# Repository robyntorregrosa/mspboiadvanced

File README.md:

# mspboiadvanced
a handheld game console in msp430 

table of contents:

gameboi.c - this is the important part of the project that runs the game on the LED board

rand.c - used for randomly placing berries on the board

snake.c - attempt at making a FIFO snake struct

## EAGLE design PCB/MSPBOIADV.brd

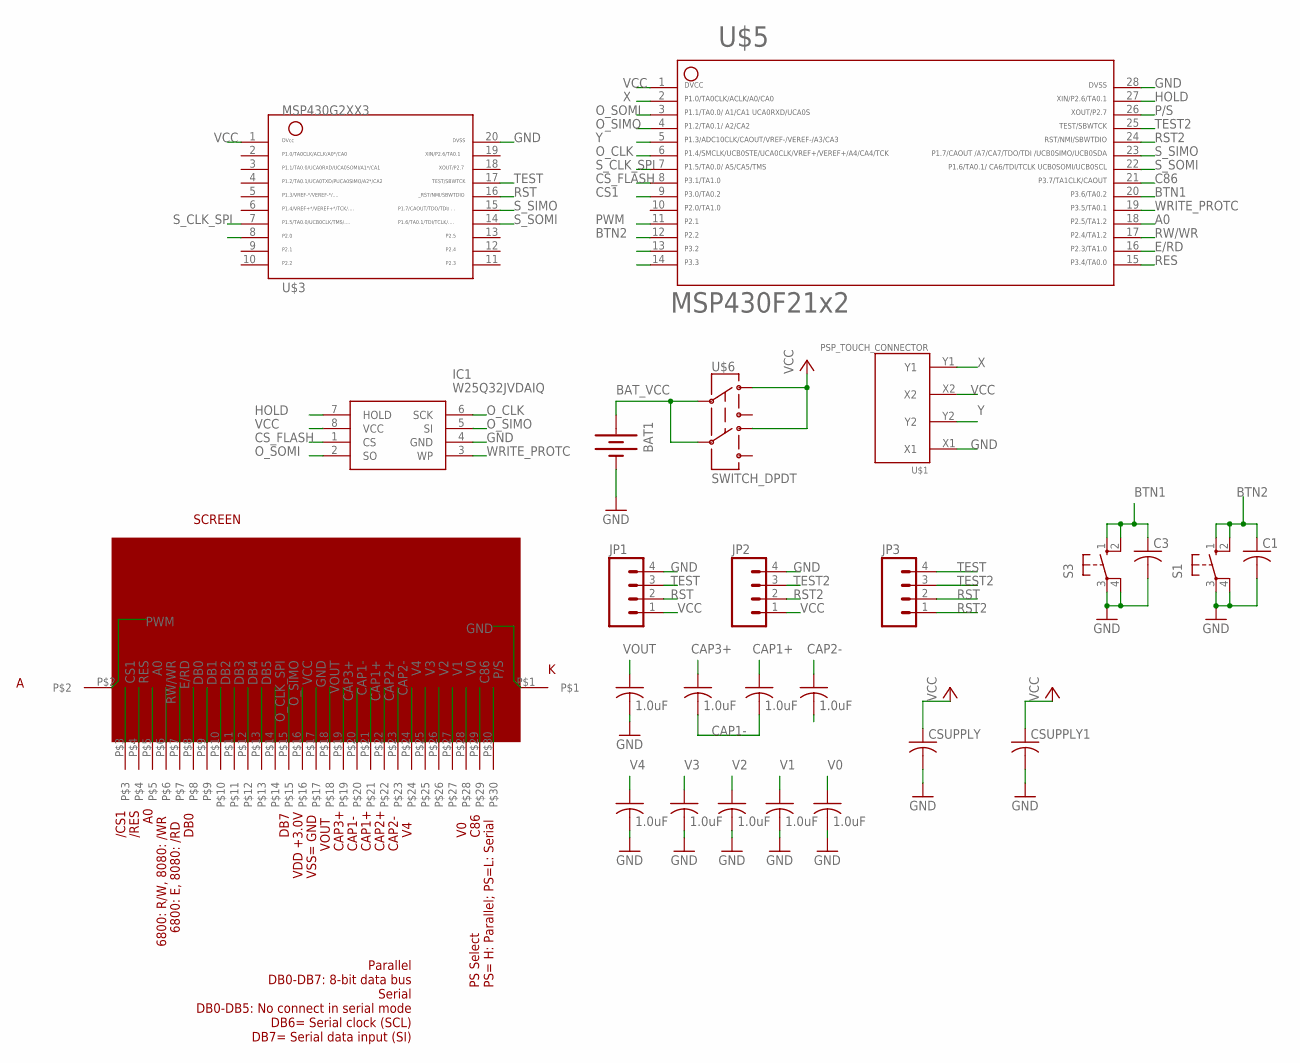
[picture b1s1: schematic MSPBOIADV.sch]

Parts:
1.0UF, 1.0UF1: 1.0uF; C1206
BAT1: BATTERY; BATTERY_PACK_2AA
C1, C3: C-USC1206; C1206
CSUPPLY, CSUPPLY1: C-USC1206; C1206
IC1: W25Q32JVDAIQ; DIP902W46P254L959H533Q8N
JP1, JP2, JP3: M04LOCK; 1X04_LOCK
S1, S3: 10-XX; B3F-10XX
U$1: PSP_TOUCH_CONNECTOR
U$2: SCREEN; DISPLAY_128_64
U$3: MSP430G2XX3TSSOP; PW20
U$5: USETHIS; PW28
U$6: SWITCH_DPDT; JS_DPDT_TH
VOUTCAP, VOUTCAP1, VOUTCAP2, VOUTCAP3, VOUTCAP4, VOUTCAP5, VOUTCAP6: 1.0uF; C1206

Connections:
A0: U$2.P$5, U$5.18
BAT_VCC: BAT1.3V (+), U$6.2, U$6.5
BTN1: C3.1, S3.1 (S), S3.2 (S1), U$5.20
BTN2: C1.1, S1.1 (S), S1.2 (S1), U$5.12
C86: U$2.P$29, U$5.21
CAP1+: 1.0UF1.1, U$2.P$21
CAP1-: 1.0UF.2, 1.0UF1.2, U$2.P$20
CAP2+: U$2.P$22, VOUTCAP1.2
CAP2-: U$2.P$23, VOUTCAP1.1
CAP3+: 1.0UF.1, U$2.P$19
CHP_SLCT: U$3.8
CS1: U$2.P$3, U$5.9
CS_FLASH: IC1.1 (CS), U$5.8
DB0: U$2.P$8
DB1: U$2.P$9
DB2: U$2.P$10
DB3: U$2.P$11
DB4: U$2.P$12
DB5: U$2.P$13
E/RD: U$2.P$7, U$5.16
GND: BAT1.GND (-), C1.2, C3.2, CSUPPLY.2, CSUPPLY1.2, IC1.4 (GND), JP1.4, JP2.4, S1.3, S1.4 (P1), S3.3, S3.4 (P1), U$1.X1, U$2.P$1, U$2.P$17, U$3.20, U$5.28, VOUTCAP.2, VOUTCAP2.2, VOUTCAP3.2, VOUTCAP4.2, VOUTCAP5.2, VOUTCAP6.2
HOLD: IC1.7 (HOLD), U$5.27
O_CLK: IC1.6 (SCK), U$5.6
O_CLK_SPI: U$2.P$14
O_SIMO: IC1.5 (SI), U$2.P$15, U$5.4
O_SOMI: IC1.2 (SO), U$5.3
P/S: U$2.P$30, U$5.26
PWM: U$2.P$2, U$5.11
RES: U$2.P$4, U$5.15
RST: JP1.2, JP3.2, U$3.16
RST2: JP2.2, JP3.1, U$5.24
RW/WR: U$2.P$6, U$5.17
S_CLK_SPI: U$3.7, U$5.7
S_SIMO: U$3.15, U$5.23
S_SOMI: U$3.14, U$5.22
TEST: JP1.3, JP3.4, U$3.17
TEST2: JP2.3, JP3.3, U$5.25
V0: U$2.P$28, VOUTCAP6.1
V1: U$2.P$27, VOUTCAP5.1
V2: U$2.P$26, VOUTCAP4.1
V3: U$2.P$25, VOUTCAP3.1
V4: U$2.P$24, VOUTCAP2.1
VCC: CSUPPLY.1, CSUPPLY1.1, IC1.8 (VCC), JP1.1, JP2.1, U$1.X2, U$2.P$16, U$3.1, U$5.1, U$6.1, U$6.4
VOUT: U$2.P$18, VOUTCAP.1
WRITE_PROTC: IC1.3 (WP), U$5.19
X: U$1.Y1, U$5.2
Y: U$1.Y2, U$5.5

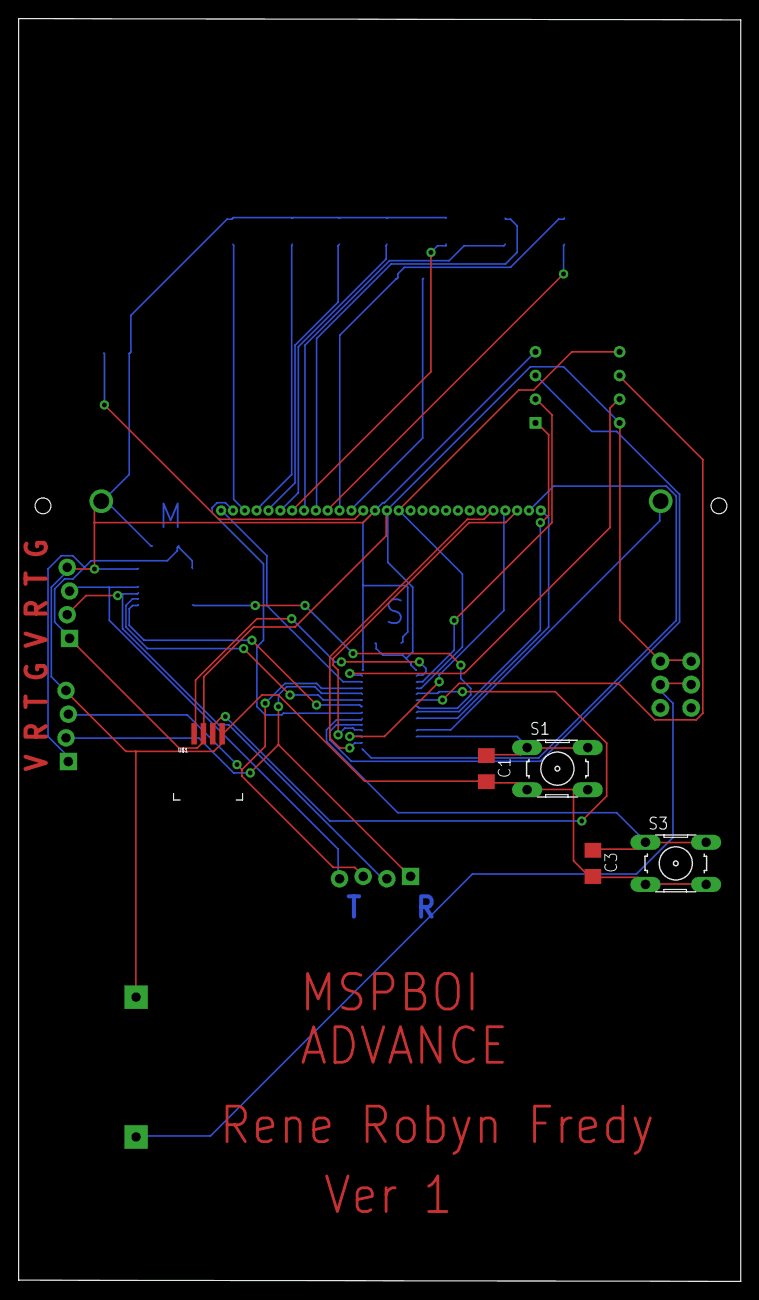
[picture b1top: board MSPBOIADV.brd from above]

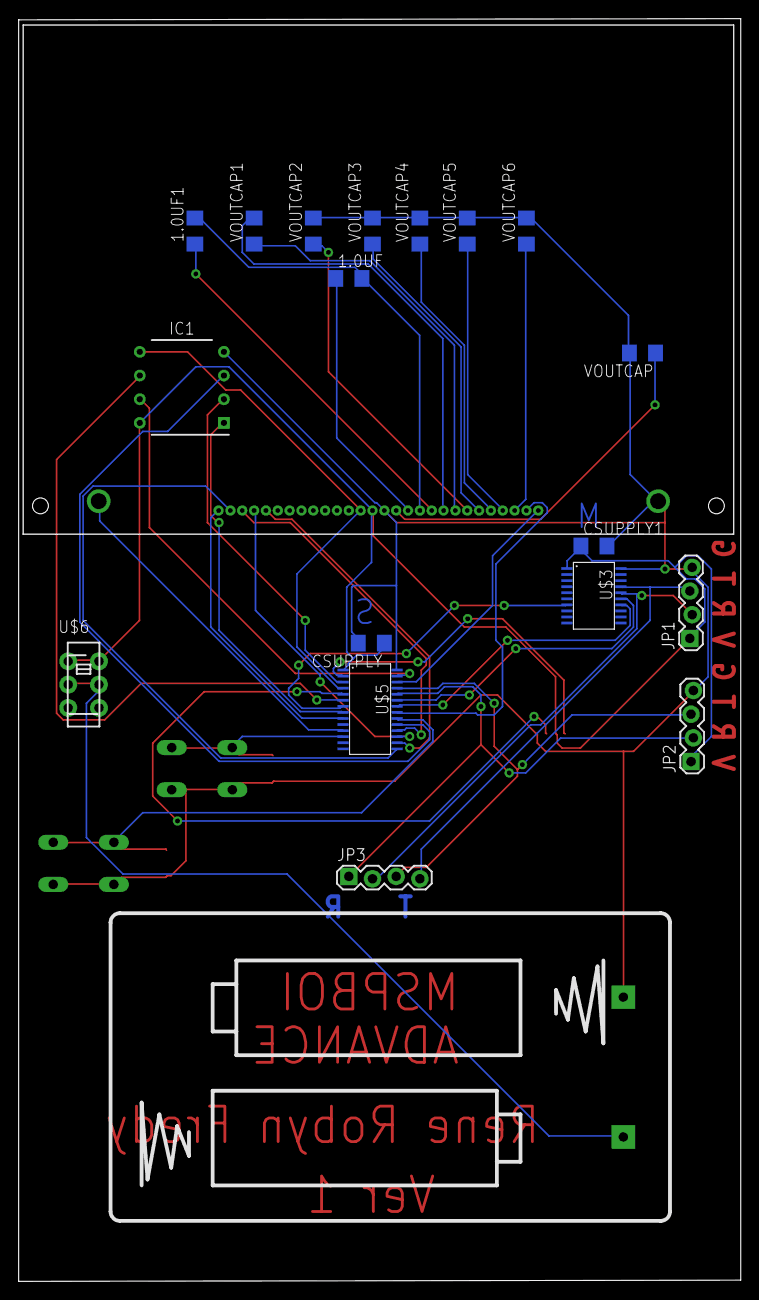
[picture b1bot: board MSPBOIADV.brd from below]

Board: 2 copper layers, 77.4 x 135.4 mm, 25 parts (20 on the bottom side), 39 nets.

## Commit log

2019-04-18 screen datasheet
2019-04-18 initial commit parts lib
2019-04-18 Add MSP430QFN Datasheet
2019-04-19 screen eagle part
2019-04-19 add sparkfun EAGLE library (with JOYSTICK-PSP1000 part) and joystick datasheet
2019-04-19 Add ELEC 327 Parts and QFN Package
2019-04-19 JTAG resources... void ProgramFinalProject(int addr)
2019-04-19 Add Flash Storage Datasheet
2019-04-19 Add files via upload
    Fixed board, added 28 pin MSP, and through hole flash chip
2019-04-19 Route Board
2019-04-21 add general blink.c project for msp and msp430 user guide
2019-04-22 add x,y joystick read to ADC10
2019-04-22 Revert "add general blink.c project for msp and msp430 user guide"
    This reverts commit 88c413f6703c08069f4096d2057f1f2f74dd72a3.
2019-04-22 organize PCB files into new folder
2019-04-27 setup SPI (S + O), setup buttons (BTN1 = P2.2) (known issue where BTN1 is on port 3 which does not have interrupt), setup P2.1 as PWM
2019-04-28 Add setup functions for the display
2019-04-29 add pin descriptions for screen mode settings
2019-04-29 Backlight
    confirms that backlight works
2019-04-29 Refactor functions and fix SPI pin setup
2019-04-29 Small test modifications
2019-04-29 No spi, bitbang
    bitbang attempt https://www.circuitvalley.com/2012/09/st7565-lcd-interfacing-msp430-pic18-avr.html
2019-04-30 Attempt 2 at getting screen to work
    https://forum.43oh.com/topic/8540-tiny-chip-on-glass-lcd-with-st7565-controller/
2019-04-30 untested snake FIFO structure (need to change storage container type to fit format of LEDs)
2019-04-30 Add Snake LED Matrix.c for working with LED matrix
2019-05-01 Add shiftPixel() function
2019-05-01 Minor fix to shiftPixel()
2019-05-01 Fix for wraparound cases not working
2019-05-01 Testing changes
2019-05-01 add rand coin
2019-05-01 xy joystick
2019-05-01 Joystick Functioning
    Adds functioning Joystick code, make a function.
2019-05-01 Update for merge
2019-05-01 Joystick input
    Adds few lines for joystick input. Still some fluctuation.
2019-05-01 new lfsr from wiki
2019-05-01 move declarations to right part of snek.c
2019-05-01 SPI plus button
2019-05-01 Working game
    Tested and filmed, minimum viable product.
2019-05-01 Update gameboi.c
    more coins at the start
2019-05-01 check if next space is a coin, eat the coin and put out a new one
2019-05-01 red berries, blue berries, die and reset
2019-05-02 change to interrupts not delay_cycles
2019-05-02 start of FIFO, not debugged
2019-05-02 something is a little bit off with that FIFO
